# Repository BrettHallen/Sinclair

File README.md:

# Sinclair
Projects for Sinclair computers (ZX80, ZX81, TS1000, TS1500, TS2068, Spectrum and clones such as the Minstrel 2 & 3).

Note!<br>
These projects maybe work-in-progress and thus not completed or fully tested!

## TS1500 Extender
Check out the ZX81 bus extender [here](https://github.com/zxinfo-diy-electronics/zx81-bus-extender) - should do the job!

## [ZX80 Gaming Keyboard](/ZX80_Gaming_Keyboard)
The cursor keys on a ZX80/ZX81 are the 5/6/7/8 numeric keys along the top row.  My simple brain can't readily adapt to this in games like ZX80 KONG or PACMAN so this is just a ZX80/ZX81 compatible keyboard with additional cursor keys.  Designed initially for use with the Minstrel 2 computer (ZX80), but can also be used with the ZX80, Minstrel 3/ZX81 and Minstrel 4th/Jupiter Ace.

### Video
- [Minstrel 2 (Sinclair ZX80 Clone): Part 3 (Gaming Keyboard)](https://youtu.be/veES_CpFuDQ)
- [Gaming Keyboard for ZX80/ZX81/Minstrel/Jupiter Ace: Part 1 (Minstrel 2 Test)](https://youtu.be/O0Em2sR0H4w)

## [ZX80 Pixel Synch](/ZX80_Pixel_Sync)
Small daughterboard to fix the [ZX80's pixel synchronisation](http://blog.tynemouthsoftware.co.uk/2022/09/minstrel-2-pixel-synchronisation-part-1.html) issue on the Minstrel 2 computer v2.8 or earlier.  I have a v2.6 board.  

### Video
[Minstrel 2 (Sinclair ZX80 Clone): Part 2 (Pixel Synch. Issue)](https://youtu.be/O-Urgigq2Vk)

## [ZX81 Centronics](/ZX81_Centronics)
Recreating a DIY centronics interface from German computer magazine c't.<br>

## [ZX81 RAM Upgrade](/ZX81_RAM_Upgrade)
Yes, yes, it's been done many times before.<br>

## [Z88 Serial Port Converter (DE9-to-DB25)](/Z88_Serial_DE9-to-DB25)
I'm finally getting my hands on a Cambridge Computers Z88.  I realised that the [Universal Backpack Drive (UBPD)](https://www.soigeneris.com/universal-backpack-drive) I have for the NEC-PC8201A will also work on the Z88 but requires a converter board.  It's possible to order one from Soigeneris when you order a UBPD and there is an existing design available on [Github](https://github.com/bkw777/Z88_RS232), but I thought I'd also have a crack at it.

### Video
[Cambridge Computer Z88: Part 2 (Backpack Drive - First Attempt)](https://youtu.be/SjToMHrZwcI)

## [Z88 Serial Port Converter (DE9-to-DE9)](/Z88_Serial_DE9_Converter)
Simple board to convert Z88 DE9 serial port to standard DE9 to use with Serial-to-USB converter, for example.

## [Z88 Mechanical Keyboard](/Z88_Mechanical_Keyboard)
The original keyboard on my Z88 seems a bit flaky - let's try designing a nice, modern replacement.

## [VDrive Serial Interface for Z88](/VDriveZ88_Serial_Converter)
Serial interface converter for the Z88 to use a VDrive.

## [ZX26 Computer](/https://github.com/BrettHallen/ZX26_Computer)
My attempt at a ZX81 clone using the vLA81.

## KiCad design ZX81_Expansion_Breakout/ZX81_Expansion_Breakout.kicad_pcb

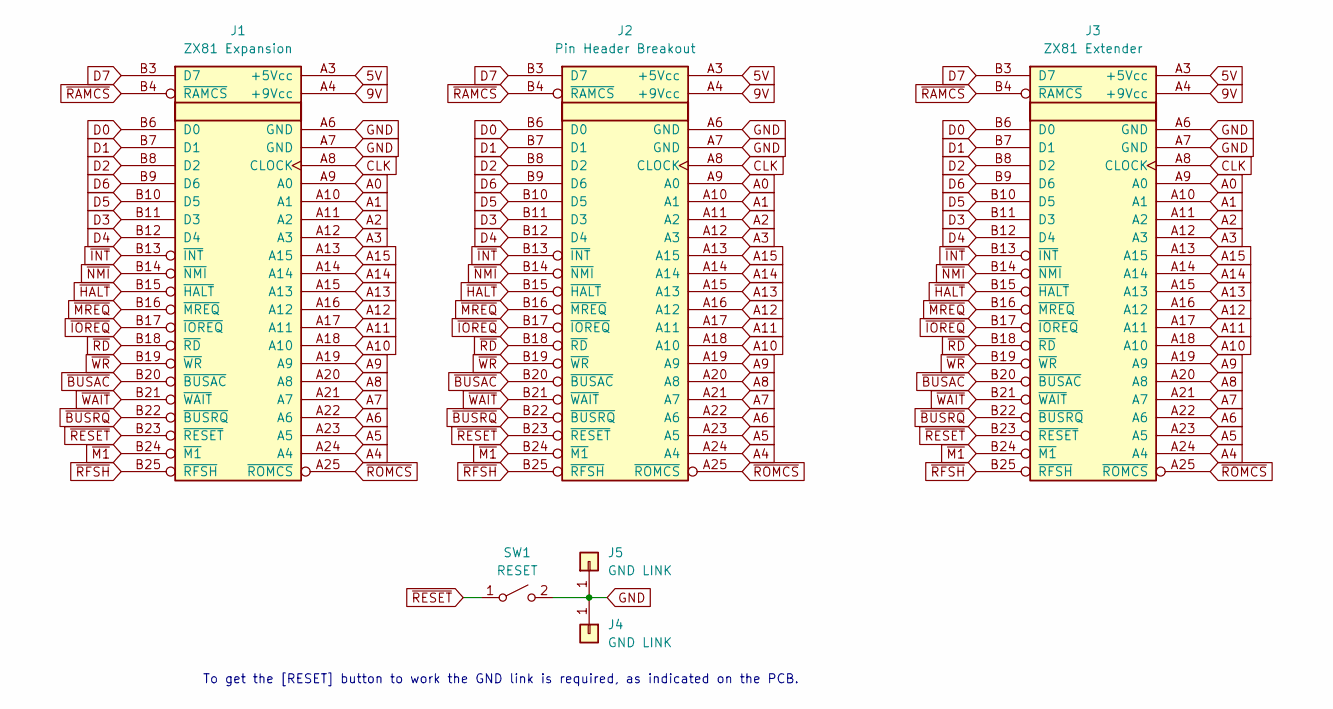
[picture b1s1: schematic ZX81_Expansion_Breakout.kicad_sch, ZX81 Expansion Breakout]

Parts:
J1: ZX81 Expansion; EDGE ZX81 BOTTOM
J2: Pin Header Breakout; PinHeader_2x23_P2.54mm_Vertical
J3: ZX81 Extender; EDGE ZX81 TOP
J4, J5: GND LINK; PinHeader_1x01_P2.54mm_Vertical
SW1: RESET; SW_PUSH_6mm

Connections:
5V: J1.A3 (+5Vcc), J2.A3 (+5Vcc), J3.A3 (+5Vcc)
9V: J1.A4 (+9Vcc), J2.A4 (+9Vcc), J3.A4 (+9Vcc)
A0: J1.A9 (A0), J2.A9 (A0), J3.A9 (A0)
A1: J1.A10 (A1), J2.A10 (A1), J3.A10 (A1)
A2: J1.A11 (A2), J2.A11 (A2), J3.A11 (A2)
A3: J1.A12 (A3), J2.A12 (A3), J3.A12 (A3)
A4: J1.A24 (A4), J2.A24 (A4), J3.A24 (A4)
A5: J1.A23 (A5), J2.A23 (A5), J3.A23 (A5)
A6: J1.A22 (A6), J2.A22 (A6), J3.A22 (A6)
A7: J1.A21 (A7), J2.A21 (A7), J3.A21 (A7)
A8: J1.A20 (A8), J2.A20 (A8), J3.A20 (A8)
A9: J1.A19 (A9), J2.A19 (A9), J3.A19 (A9)
A10: J1.A18 (A10), J2.A18 (A10), J3.A18 (A10)
A11: J1.A17 (A11), J2.A17 (A11), J3.A17 (A11)
A12: J1.A16 (A12), J2.A16 (A12), J3.A16 (A12)
A13: J1.A15 (A13), J2.A15 (A13), J3.A15 (A13)
A14: J1.A14, J2.A14, J3.A14
A15: J1.A13 (A15), J2.A13 (A15), J3.A13 (A15)
CLK: J1.A8 (CLOCK), J2.A8 (CLOCK), J3.A8 (CLOCK)
D0: J1.B6 (D0), J2.B6 (D0), J3.B6 (D0)
D1: J1.B7 (D1), J2.B7 (D1), J3.B7 (D1)
D2: J1.B8 (D2), J2.B8 (D2), J3.B8 (D2)
D3: J1.B11 (D3), J2.B11 (D3), J3.B11 (D3)
D4: J1.B12 (D4), J2.B12 (D4), J3.B12 (D4)
D5: J1.B10 (D5), J2.B10 (D5), J3.B10 (D5)
D6: J1.B9 (D6), J2.B9 (D6), J3.B9 (D6)
D7: J1.B3 (D7), J2.B3 (D7), J3.B3 (D7)
GND: J1.A6 (GND), J1.A7 (GND), J2.A6 (GND), J2.A7 (GND), J3.A6 (GND), J3.A7 (GND), J4.1 (Pin_1_1), J5.1 (Pin_1_1), SW1.2 (B)
~BUSAC: J1.B20 (~BUSAC), J2.B20 (~BUSAC), J3.B20 (~BUSAC)
~BUSRQ: J1.B22 (~BUSRQ), J2.B22 (~BUSRQ), J3.B22 (~BUSRQ)
~HALT: J1.B15 (~HALT), J2.B15 (~HALT), J3.B15 (~HALT)
~INT: J1.B13 (~INT), J2.B13 (~INT), J3.B13 (~INT)
~IOREQ: J1.B17 (~IOREQ), J2.B17 (~IOREQ), J3.B17 (~IOREQ)
~M1: J1.B24 (~M1), J2.B24 (~M1), J3.B24 (~M1)
~MREQ: J1.B16 (~MREQ), J2.B16 (~MREQ), J3.B16 (~MREQ)
~NMI: J1.B14 (~NMI), J2.B14 (~NMI), J3.B14 (~NMI)
~RAMCS: J1.B4 (~RAMCS), J2.B4 (~RAMCS), J3.B4 (~RAMCS)
~RD: J1.B18 (~RD), J2.B18 (~RD), J3.B18 (~RD)
~RESET: J1.B23 (~RESET), J2.B23 (~RESET), J3.B23 (~RESET), SW1.1 (A)
~RFSH: J1.B25 (~RFSH), J2.B25 (~RFSH), J3.B25 (~RFSH)
~ROMCS: J1.A25 (~ROMCS), J2.A25 (~ROMCS), J3.A25 (~ROMCS)
~WAIT: J1.B21 (~WAIT), J2.B21 (~WAIT), J3.B21 (~WAIT)
~WR: J1.B19 (~WR), J2.B19 (~WR), J3.B19 (~WR)

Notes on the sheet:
To get the [RESET] button to work the GND link is required, as indicated on the PCB.

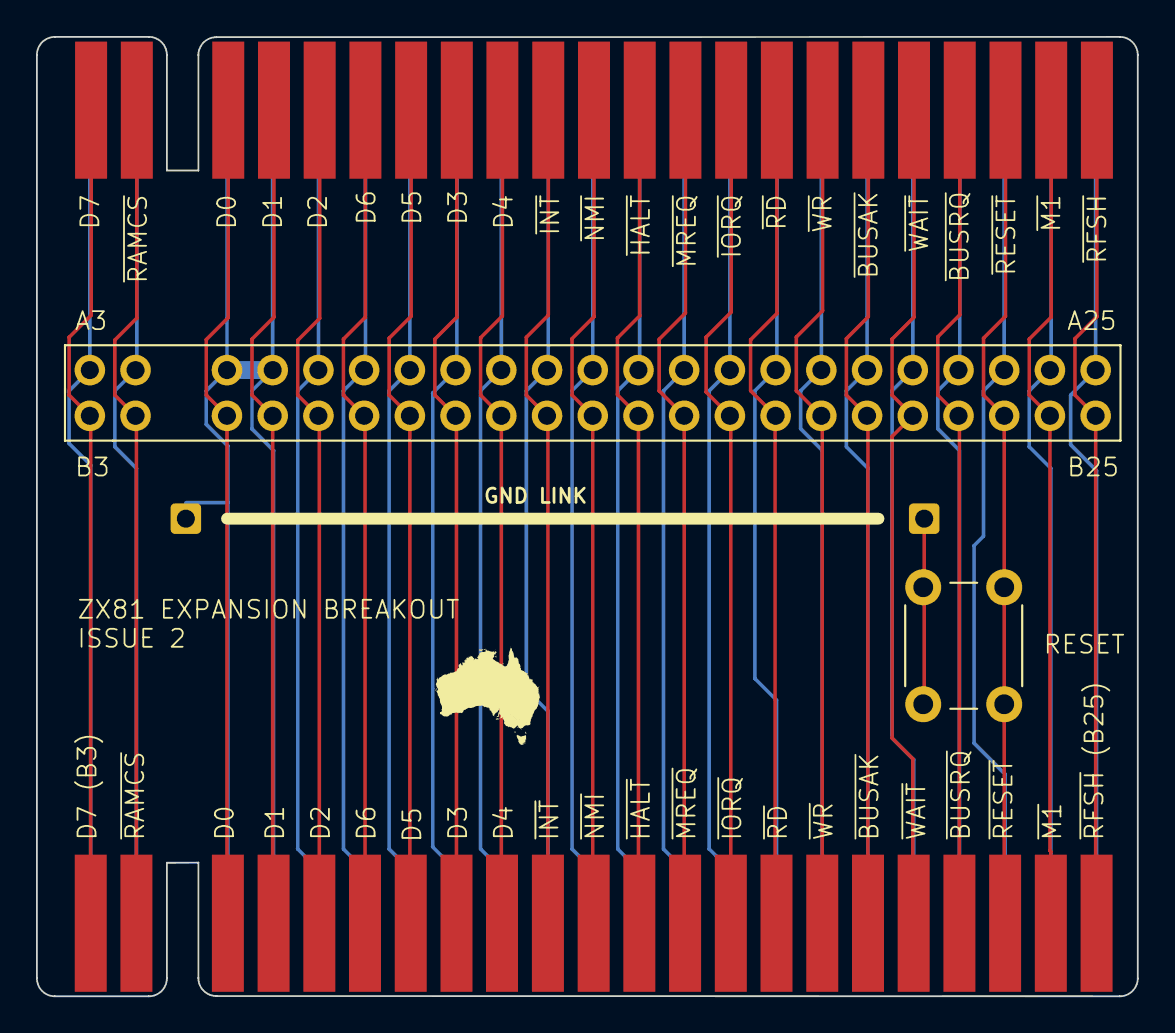
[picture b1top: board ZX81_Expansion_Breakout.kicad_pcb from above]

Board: 2 copper layers, 61.2 x 53.3 mm, 6 parts (0 on the bottom side), 43 nets.

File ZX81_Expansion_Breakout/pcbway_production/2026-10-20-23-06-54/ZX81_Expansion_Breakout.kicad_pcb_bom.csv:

Designator,Quantity,Value,Footprint,Package,MPN,DNP,Mount_Type,Field4,KiLib_Generator,Field5,Description
J1,1,ZX81 Expansion,EDGE ZX81 BOTTOM,,,,tht,SLOT,,,
J2,1,Pin Header Breakout,PinHeader_2x23_P2.54mm_Vertical,,,,tht,,connector/pin_header_socket,,
J3,1,ZX81 Extender,EDGE ZX81 TOP,,,,tht,SLOT,,SLOT,
"J4, J5",2,GND LINK,PinHeader_1x01_P2.54mm_Vertical,,,,tht,,connector/pin_header_socket,,"Generic connector, single row, 01x01, script generated (kicad-library-utils/schlib/autogen/connector/)"
R2,1,LINK,PinHeader_1x02_P2.54mm_Vertical,,,,tht,,connector/pin_header_socket,,Resistor
SW1,1,RESET,SW_PUSH_6mm,,,,tht,,,,Single Pole Single Throw (SPST) switch

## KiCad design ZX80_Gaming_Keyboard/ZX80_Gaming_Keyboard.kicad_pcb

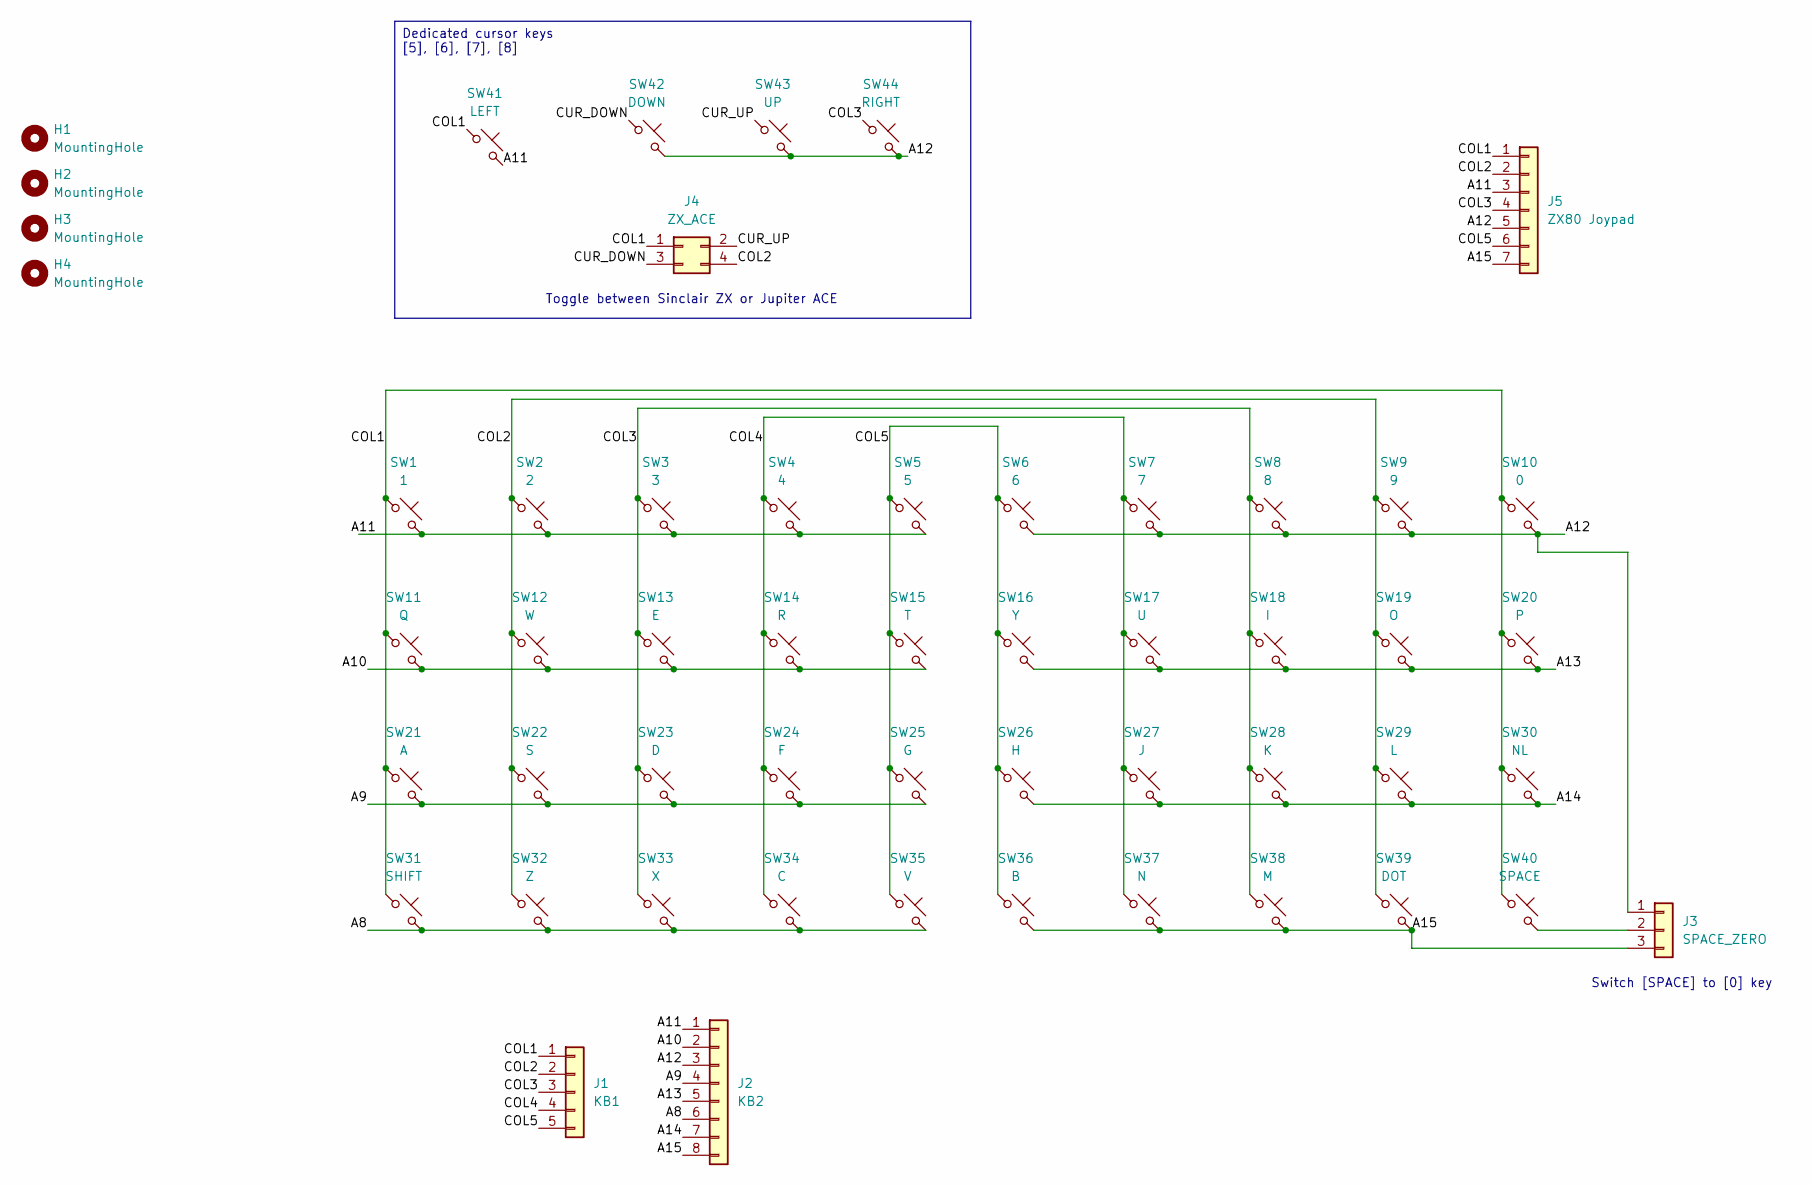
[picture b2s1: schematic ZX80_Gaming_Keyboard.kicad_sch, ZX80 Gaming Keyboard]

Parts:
H1, H2, H3, H4: MountingHole; MountingHole_3.2mm_M3
J1: KB1; PinHeader_1x05_P2.54mm_Vertical
J2: KB2; PinHeader_1x08_P2.54mm_Vertical
J3: SPACE_ZERO; PinHeader_1x03_P2.54mm_Vertical
J4: ZX_ACE; PinHeader_2x02_P2.54mm_Vertical
J5: ZX80 Joypad; PinHeader_1x07_P2.54mm_Vertical
SW1: 1; SW_PUSH-12mm
SW2: 2; SW_PUSH-12mm
SW3: 3; SW_PUSH-12mm
SW4: 4; SW_PUSH-12mm
SW5: 5; SW_PUSH-12mm
SW6: 6; SW_PUSH-12mm
SW7: 7; SW_PUSH-12mm
SW8: 8; SW_PUSH-12mm
SW9: 9; SW_PUSH-12mm
SW10: 0; SW_PUSH-12mm
SW11: Q; SW_PUSH-12mm
SW12: W; SW_PUSH-12mm
SW13: E; SW_PUSH-12mm
SW14: R; SW_PUSH-12mm
SW15: T; SW_PUSH-12mm
SW16: Y; SW_PUSH-12mm
SW17: U; SW_PUSH-12mm
SW18: I; SW_PUSH-12mm
SW19: O; SW_PUSH-12mm
SW20: P; SW_PUSH-12mm
SW21: A; SW_PUSH-12mm
SW22: S; SW_PUSH-12mm
SW23: D; SW_PUSH-12mm
SW24: F; SW_PUSH-12mm
SW25: G; SW_PUSH-12mm
SW26: H; SW_PUSH-12mm
SW27: J; SW_PUSH-12mm
SW28: K; SW_PUSH-12mm
SW29: L; SW_PUSH-12mm
SW30: NL; SW_PUSH-12mm
SW31: SHIFT; SW_PUSH-12mm
SW32: Z; SW_PUSH-12mm
SW33: X; SW_PUSH-12mm
SW34: C; SW_PUSH-12mm
SW35: V; SW_PUSH-12mm
SW36: B; SW_PUSH-12mm
SW37: N; SW_PUSH-12mm
SW38: M; SW_PUSH-12mm
SW39: DOT; SW_PUSH-12mm
SW40: SPACE; SW_PUSH-12mm
SW41: LEFT; SW_PUSH-12mm
SW42: DOWN; SW_PUSH-12mm
SW43: UP; SW_PUSH-12mm
SW44: RIGHT; SW_PUSH-12mm

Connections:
/A8: J2.6, SW31.2, SW32.2, SW33.2, SW34.2, SW35.2
/A9: J2.4, SW21.2, SW22.2, SW23.2, SW24.2, SW25.2
/A10: J2.2, SW11.2, SW12.2, SW13.2, SW14.2, SW15.2
/A11: J2.1, J5.3, SW1.2, SW2.2, SW3.2, SW4.2, SW5.2, SW41.2
/A12: J2.3, J3.1, J5.5, SW6.2, SW7.2, SW8.2, SW9.2, SW10.2, SW42.2, SW43.2, SW44.2
/A13: J2.5, SW16.2, SW17.2, SW18.2, SW19.2, SW20.2
/A14: J2.7, SW26.2, SW27.2, SW28.2, SW29.2, SW30.2
/A15: J2.8, J3.3, J5.7, SW36.2, SW37.2, SW38.2, SW39.2
/COL1: J1.1, J4.1, J5.1, SW1.1, SW10.1, SW11.1, SW20.1, SW21.1, SW30.1, SW31.1, SW40.1, SW41.1
/COL2: J1.2, J4.4, J5.2, SW2.1, SW9.1, SW12.1, SW19.1, SW22.1, SW29.1, SW32.1, SW39.1
/COL3: J1.3, J5.4, SW3.1, SW8.1, SW13.1, SW18.1, SW23.1, SW28.1, SW33.1, SW38.1, SW44.1
/COL4: J1.4, SW4.1, SW7.1, SW14.1, SW17.1, SW24.1, SW27.1, SW34.1, SW37.1
/COL5: J1.5, J5.6, SW5.1, SW6.1, SW15.1, SW16.1, SW25.1, SW26.1, SW35.1, SW36.1
/CUR_DOWN: J4.3, SW42.1
/CUR_UP: J4.2, SW43.1
unnamed: J3.2, SW40.2

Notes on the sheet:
Toggle between Sinclair ZX or Jupiter ACE
Switch [SPACE] to [0] key
Dedicated cursor keys [5], [6], [7], [8]

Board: 2 copper layers, 53 parts (0 on the bottom side), 16 nets, no tracks yet.

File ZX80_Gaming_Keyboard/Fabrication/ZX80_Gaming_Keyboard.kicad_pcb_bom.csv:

Designator,Quantity,Value,Footprint,Package,MPN,DNP,Mount_Type,Description
J1,1,KB1,PinHeader_1x05_P2.54mm_Vertical,,,,tht,"Generic connector, single row, 01x05, script generated (kicad-library-utils/schlib/autogen/connector/)"
J2,1,KB2,PinHeader_1x08_P2.54mm_Vertical,,,,tht,"Generic connector, single row, 01x08, script generated (kicad-library-utils/schlib/autogen/connector/)"
J3,1,SPACE_ZERO,PinHeader_1x03_P2.54mm_Vertical,,,,tht,"Generic connector, single row, 01x03, script generated (kicad-library-utils/schlib/autogen/connector/)"
J4,1,ZX_ACE,PinHeader_2x02_P2.54mm_Vertical,,,,tht,"Generic connector, double row, 02x02, odd/even pin numbering scheme (row 1 odd numbers, row 2 even numbers), script generated (kicad-library-utils/schlib/autogen/connector/)"
SW1,1,1,SW_Cherry_MX_1.00u_PCB,,,,tht,"Push button switch, normally open, two pins, 45° tilted"
SW10,1,0,SW_Cherry_MX_1.00u_PCB,,,,tht,"Push button switch, normally open, two pins, 45° tilted"
SW11,1,Q,SW_Cherry_MX_1.00u_PCB,,,,tht,"Push button switch, normally open, two pins, 45° tilted"
SW12,1,W,SW_Cherry_MX_1.00u_PCB,,,,tht,"Push button switch, normally open, two pins, 45° tilted"
SW13,1,E,SW_Cherry_MX_1.00u_PCB,,,,tht,"Push button switch, normally open, two pins, 45° tilted"
SW14,1,R,SW_Cherry_MX_1.00u_PCB,,,,tht,"Push button switch, normally open, two pins, 45° tilted"
SW15,1,T,SW_Cherry_MX_1.00u_PCB,,,,tht,"Push button switch, normally open, two pins, 45° tilted"
SW16,1,Y,SW_Cherry_MX_1.00u_PCB,,,,tht,"Push button switch, normally open, two pins, 45° tilted"
SW17,1,U,SW_Cherry_MX_1.00u_PCB,,,,tht,"Push button switch, normally open, two pins, 45° tilted"
SW18,1,I,SW_Cherry_MX_1.00u_PCB,,,,tht,"Push button switch, normally open, two pins, 45° tilted"
SW19,1,O,SW_Cherry_MX_1.00u_PCB,,,,tht,"Push button switch, normally open, two pins, 45° tilted"
SW2,1,2,SW_Cherry_MX_1.00u_PCB,,,,tht,"Push button switch, normally open, two pins, 45° tilted"
SW20,1,P,SW_Cherry_MX_1.00u_PCB,,,,tht,"Push button switch, normally open, two pins, 45° tilted"
SW21,1,A,SW_Cherry_MX_1.00u_PCB,,,,tht,"Push button switch, normally open, two pins, 45° tilted"
SW22,1,S,SW_Cherry_MX_1.00u_PCB,,,,tht,"Push button switch, normally open, two pins, 45° tilted"
SW23,1,D,SW_Cherry_MX_1.00u_PCB,,,,tht,"Push button switch, normally open, two pins, 45° tilted"
SW24,1,F,SW_Cherry_MX_1.00u_PCB,,,,tht,"Push button switch, normally open, two pins, 45° tilted"
SW25,1,G,SW_Cherry_MX_1.00u_PCB,,,,tht,"Push button switch, normally open, two pins, 45° tilted"
SW26,1,H,SW_Cherry_MX_1.00u_PCB,,,,tht,"Push button switch, normally open, two pins, 45° tilted"
SW27,1,J,SW_Cherry_MX_1.00u_PCB,,,,tht,"Push button switch, normally open, two pins, 45° tilted"
SW28,1,K,SW_Cherry_MX_1.00u_PCB,,,,tht,"Push button switch, normally open, two pins, 45° tilted"
SW29,1,L,SW_Cherry_MX_1.00u_PCB,,,,tht,"Push button switch, normally open, two pins, 45° tilted"
SW3,1,3,SW_Cherry_MX_1.00u_PCB,,,,tht,"Push button switch, normally open, two pins, 45° tilted"
SW30,1,NL,SW_Cherry_MX_1.00u_PCB,,,,tht,"Push button switch, normally open, two pins, 45° tilted"
SW31,1,SHIFT,SW_Cherry_MX_1.00u_PCB,,,,tht,"Push button switch, normally open, two pins, 45° tilted"
SW32,1,Z,SW_Cherry_MX_1.00u_PCB,,,,tht,"Push button switch, normally open, two pins, 45° tilted"
SW33,1,X,SW_Cherry_MX_1.00u_PCB,,,,tht,"Push button switch, normally open, two pins, 45° tilted"
SW34,1,C,SW_Cherry_MX_1.00u_PCB,,,,tht,"Push button switch, normally open, two pins, 45° tilted"
SW35,1,V,SW_Cherry_MX_1.00u_PCB,,,,tht,"Push button switch, normally open, two pins, 45° tilted"
SW36,1,B,SW_Cherry_MX_1.00u_PCB,,,,tht,"Push button switch, normally open, two pins, 45° tilted"
SW37,1,N,SW_Cherry_MX_1.00u_PCB,,,,tht,"Push button switch, normally open, two pins, 45° tilted"
SW38,1,M,SW_Cherry_MX_1.00u_PCB,,,,tht,"Push button switch, normally open, two pins, 45° tilted"
SW39,1,DOT,SW_Cherry_MX_1.00u_PCB,,,,tht,"Push button switch, normally open, two pins, 45° tilted"
SW4,1,4,SW_Cherry_MX_1.00u_PCB,,,,tht,"Push button switch, normally open, two pins, 45° tilted"
SW40,1,SPACE,SW_Cherry_MX_1.00u_PCB,,,,tht,"Push button switch, normally open, two pins, 45° tilted"
SW41,1,LEFT,SW_Cherry_MX_1.00u_PCB,,,,tht,"Push button switch, normally open, two pins, 45° tilted"
SW42,1,DOWN,SW_Cherry_MX_1.00u_PCB,,,,tht,"Push button switch, normally open, two pins, 45° tilted"
SW43,1,UP,SW_Cherry_MX_1.00u_PCB,,,,tht,"Push button switch, normally open, two pins, 45° tilted"
SW44,1,RIGHT,SW_Cherry_MX_1.00u_PCB,,,,tht,"Push button switch, normally open, two pins, 45° tilted"
SW5,1,5,SW_Cherry_MX_1.00u_PCB,,,,tht,"Push button switch, normally open, two pins, 45° tilted"
SW6,1,6,SW_Cherry_MX_1.00u_PCB,,,,tht,"Push button switch, normally open, two pins, 45° tilted"
SW7,1,7,SW_Cherry_MX_1.00u_PCB,,,,tht,"Push button switch, normally open, two pins, 45° tilted"
SW8,1,8,SW_Cherry_MX_1.00u_PCB,,,,tht,"Push button switch, normally open, two pins, 45° tilted"
SW9,1,9,SW_Cherry_MX_1.00u_PCB,,,,tht,"Push button switch, normally open, two pins, 45° tilted"

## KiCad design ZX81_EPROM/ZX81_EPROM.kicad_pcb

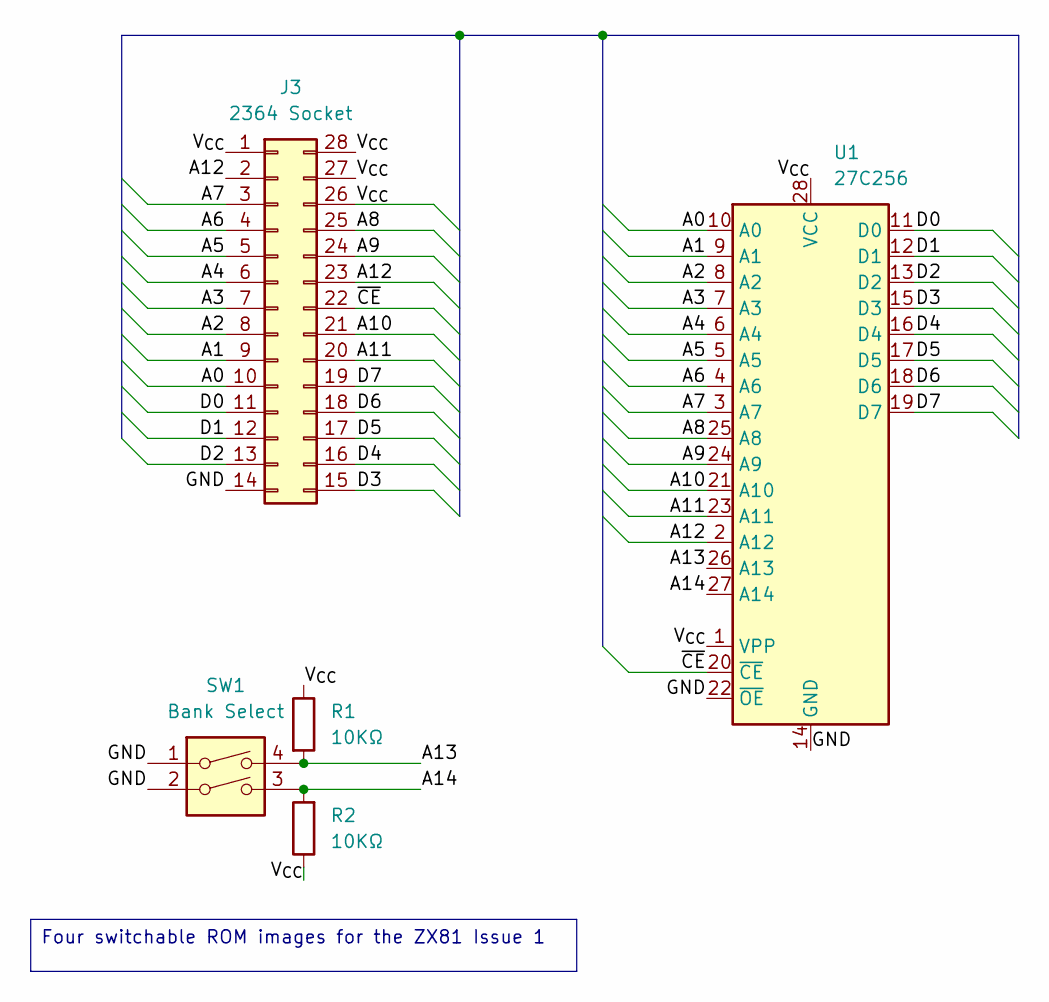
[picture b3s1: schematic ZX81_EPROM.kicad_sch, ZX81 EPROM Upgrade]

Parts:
J3: 2364 Socket; DIP-28_W15.24mm_Socket
R1, R2: 10KΩ; R_0805_2012Metric_Pad1.20x1.40mm_HandSolder
SW1: Bank Select; SW_DIP_SPSTx02_Slide_9.78x7.26mm_W7.62mm_P2.54mm
U1: 27C256; DIP-28_W15.24mm

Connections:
/A0: J3.10, U1.10 (A0)
/A1: J3.9, U1.9 (A1)
/A2: J3.8, U1.8 (A2)
/A3: J3.7, U1.7 (A3)
/A4: J3.6, U1.6 (A4)
/A5: J3.5, U1.5 (A5)
/A6: J3.4, U1.4 (A6)
/A7: J3.3, U1.3 (A7)
/A8: J3.25, U1.25 (A8)
/A9: J3.24, U1.24 (A9)
/A10: J3.21, U1.21 (A10)
/A11: J3.20, U1.23 (A11)
/A12: J3.2, J3.23, U1.2 (A12)
/A13: R1.2, SW1.4, U1.26 (A13)
/A14: R2.2, SW1.3, U1.27 (A14)
/D0: J3.11, U1.11 (D0)
/D1: J3.12, U1.12 (D1)
/D2: J3.13, U1.13 (D2)
/D3: J3.15, U1.15 (D3)
/D4: J3.16, U1.16 (D4)
/D5: J3.17, U1.17 (D5)
/D6: J3.18, U1.18 (D6)
/D7: J3.19, U1.19 (D7)
/GND: J3.14, SW1.1, SW1.2, U1.14 (GND), U1.22 (~OE)
/V_{CC}: J3.1, J3.26, J3.27, J3.28, R1.1, R2.1, U1.1 (VPP), U1.28 (VCC)
/~CE: J3.22, U1.20 (~CE)

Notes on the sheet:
Four switchable ROM images for the ZX81 Issue 1

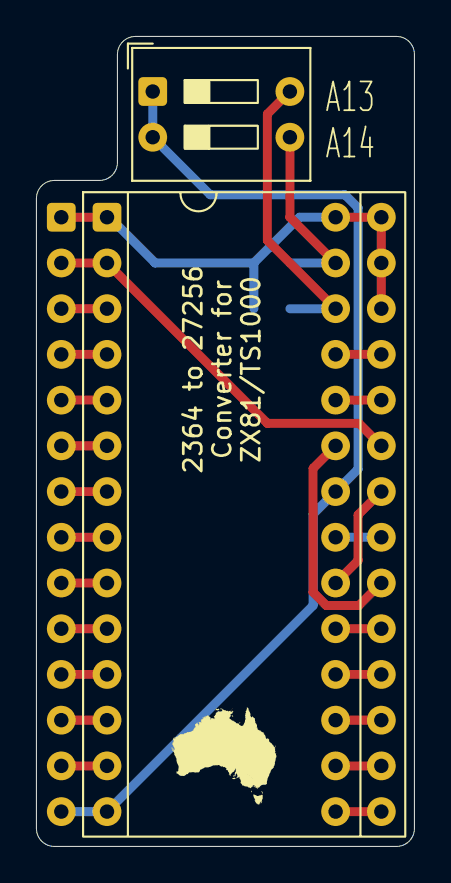
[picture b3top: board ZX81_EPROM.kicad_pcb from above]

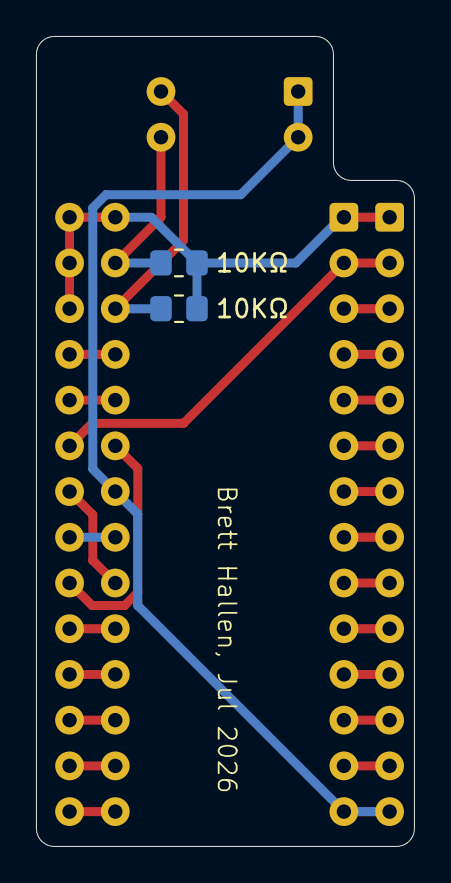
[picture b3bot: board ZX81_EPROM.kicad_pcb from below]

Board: 2 copper layers, 21.0 x 45.0 mm, 5 parts (2 on the bottom side), 26 nets.

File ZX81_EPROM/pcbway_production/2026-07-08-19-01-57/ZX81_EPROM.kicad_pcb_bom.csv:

Designator,Quantity,Value,Footprint,Package,MPN,DNP,Mount_Type,Description,KiLib_Generator
J3,1,2364 Socket,DIP-28_W15.24mm_Socket,,,,tht,"Generic connector, double row, 02x14, counter clockwise pin numbering scheme (similar to DIP package numbering), script generated (kicad-library-utils/schlib/autogen/connector/)",package/DIP/legacy
"R1, R2",2,10KΩ,R_0805_2012Metric_Pad1.20x1.40mm_HandSolder,,,,smt,Resistor,SMD_2terminal_chip_molded
SW1,1,Bank Select,SW_DIP_SPSTx02_Slide_9.78x7.26mm_W7.62mm_P2.54mm,,,,tht,"2x DIP Switch, Single Pole Single Throw (SPST) switch, small symbol",button_switch/DIP
U1,1,27C256,DIP-28_W15.24mm,,,,tht,OTP EPROM 256 KiBit,package/DIP/legacy

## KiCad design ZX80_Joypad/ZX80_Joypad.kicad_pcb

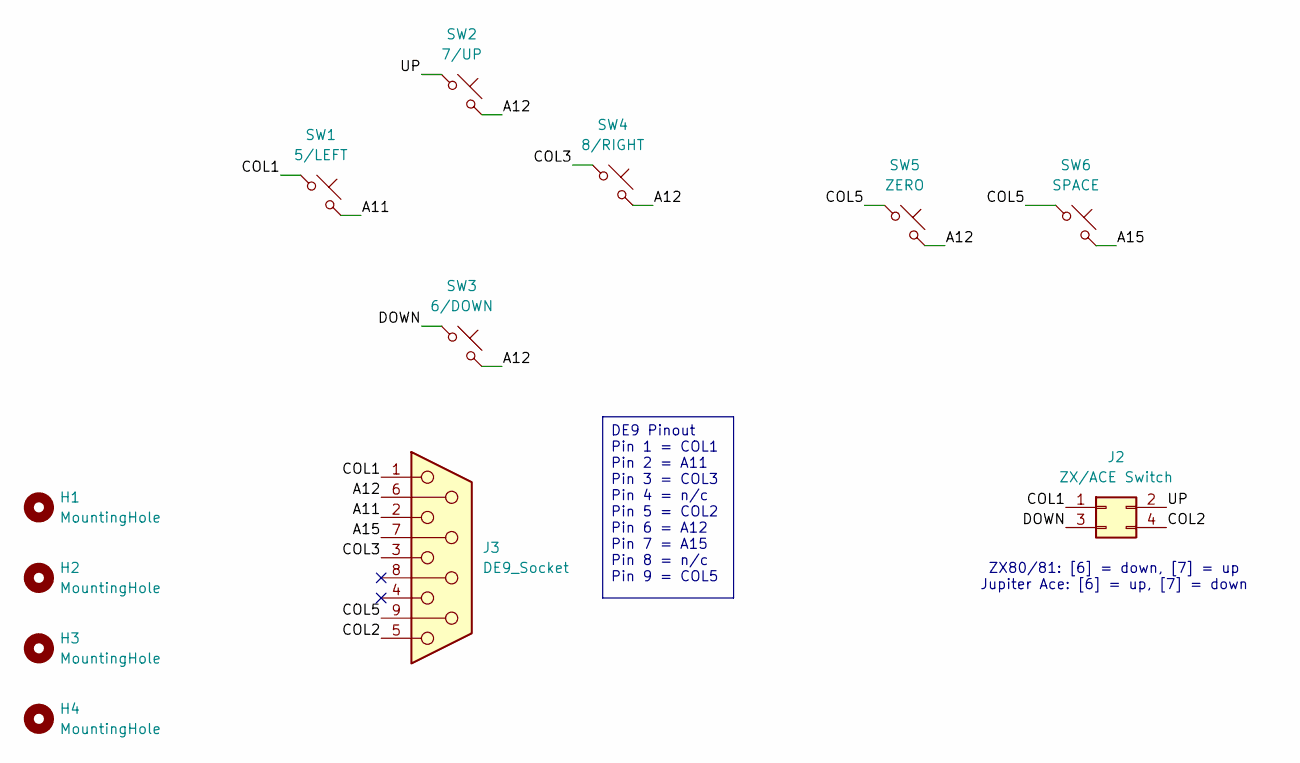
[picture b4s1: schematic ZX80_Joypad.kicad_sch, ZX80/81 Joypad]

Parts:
H1, H2, H3, H4: MountingHole; MountingHole_3.2mm_M3_DIN965
J2: ZX/ACE Switch; PinHeader_2x02_P2.54mm_Vertical
J3: DE9_Socket; DSUB-9_Socket_EdgeMount_P2.77mm
SW1: 5/LEFT; SW_PUSH-12mm
SW2: 7/UP; SW_PUSH-12mm
SW3: 6/DOWN; SW_PUSH-12mm
SW4: 8/RIGHT; SW_PUSH-12mm
SW5: ZERO; SW_PUSH-12mm
SW6: SPACE; SW_PUSH-12mm

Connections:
/A11: J3.2, SW1.2
/A12: J3.6, SW2.2, SW3.2, SW4.2, SW5.2
/A15: J3.7, SW6.2
/COL1: J2.1, J3.1, SW1.1
/COL2: J2.4, J3.5
/COL3: J3.3, SW4.1
/COL5: J3.9, SW5.1, SW6.1
/DOWN: J2.3, SW3.1
/UP: J2.2, SW2.1

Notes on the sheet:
ZX80/81: [6] = down, [7] = up Jupiter Ace: [6] = up, [7] = down
DE9 Pinout Pin 1 = COL1 Pin 2 = A11 Pin 3 = COL3 Pin 4 = n/c Pin 5 = COL2 Pin 6 = A12 Pin 7 = A15 Pin 8 = n/c Pin 9 = COL5

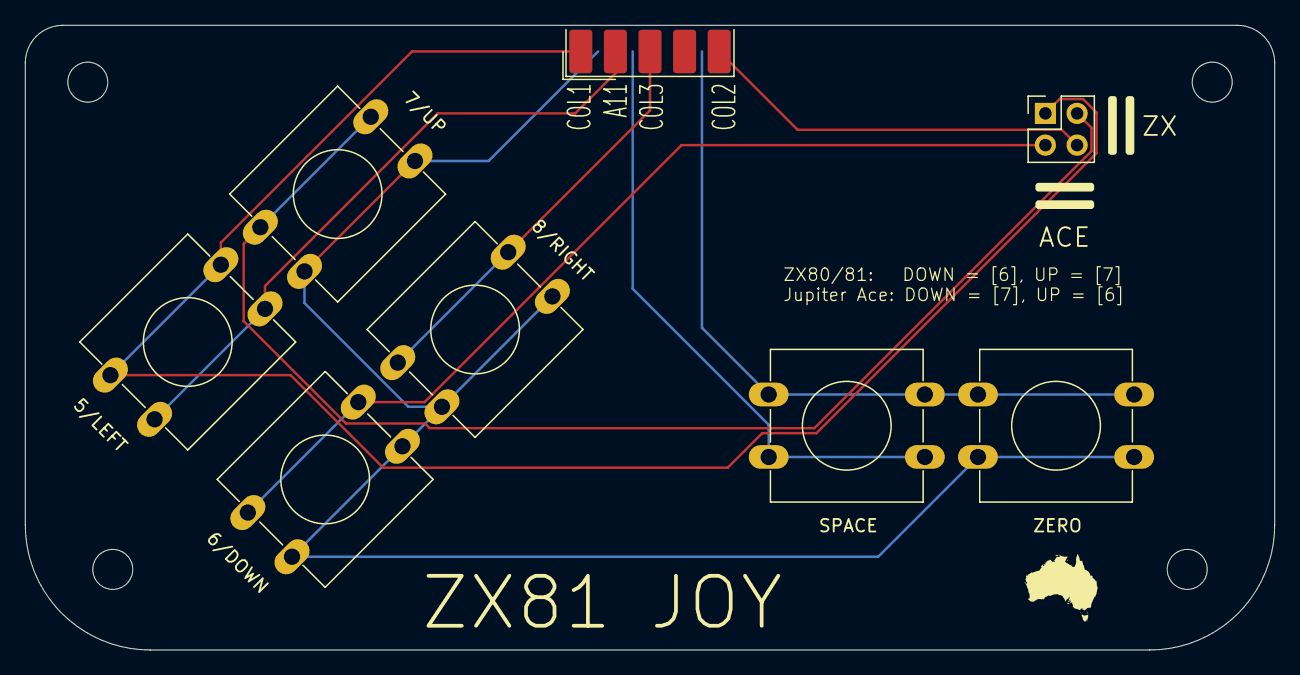
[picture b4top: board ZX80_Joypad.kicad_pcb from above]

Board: 2 copper layers, 100.0 x 50.0 mm, 12 parts (0 on the bottom side), 9 nets.

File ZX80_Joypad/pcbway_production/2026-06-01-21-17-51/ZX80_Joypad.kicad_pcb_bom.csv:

Designator,Quantity,Value,Footprint,Package,MPN,DNP,Mount_Type,Description
J1,1,Conn_02x04_Odd_Even,PinHeader_2x04_P2.54mm_Vertical,,,,tht,"Generic connector, double row, 02x04, odd/even pin numbering scheme (row 1 odd numbers, row 2 even numbers), script generated (kicad-library-utils/schlib/autogen/connector/)"
J2,1,ZX/ACE Switch,PinHeader_2x02_P2.54mm_Vertical,,,,tht,"Generic connector, double row, 02x02, odd/even pin numbering scheme (row 1 odd numbers, row 2 even numbers), script generated (kicad-library-utils/schlib/autogen/connector/)"
SW1,1,5/LEFT,SW_PUSH-12mm,,,,tht,"Push button switch, normally open, two pins, 45° tilted"
SW2,1,7/UP,SW_PUSH-12mm,,,,tht,"Push button switch, normally open, two pins, 45° tilted"
SW3,1,6/DOWN,SW_PUSH-12mm,,,,tht,"Push button switch, normally open, two pins, 45° tilted"
SW4,1,8/RIGHT,SW_PUSH-12mm,,,,tht,"Push button switch, normally open, two pins, 45° tilted"
SW5,1,ZERO,SW_PUSH-12mm,,,,tht,"Push button switch, normally open, two pins, 45° tilted"
SW6,1,SPACE,SW_PUSH-12mm,,,,tht,"Push button switch, normally open, two pins, 45° tilted"

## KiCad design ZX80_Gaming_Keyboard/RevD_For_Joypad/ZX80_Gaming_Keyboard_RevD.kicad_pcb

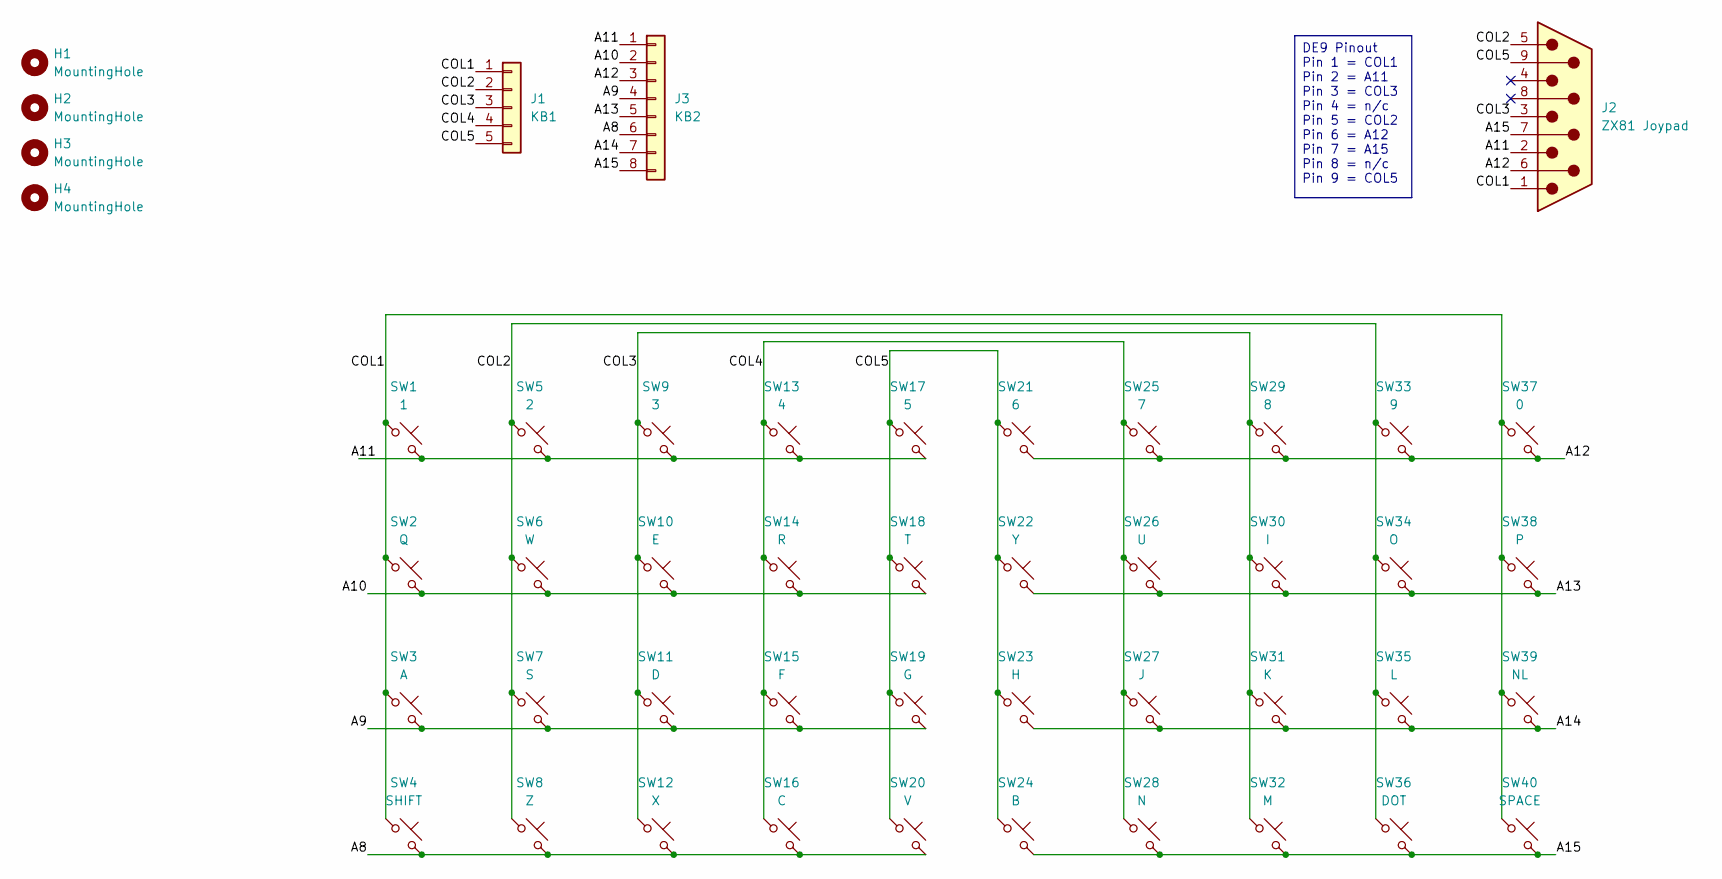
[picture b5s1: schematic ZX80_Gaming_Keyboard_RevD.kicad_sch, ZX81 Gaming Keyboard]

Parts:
H1, H2, H3, H4: MountingHole; MountingHole_3.2mm_M3
J1: KB1; PinHeader_1x05_P2.54mm_Vertical
J2: ZX81 Joypad; DSUB-9_Pins_EdgeMount_P2.77mm
J3: KB2; PinHeader_1x08_P2.54mm_Vertical
SW1: 1; SW_Gateron_LowProfile_THT
SW2: Q; SW_Gateron_LowProfile_THT
SW3: A; SW_Gateron_LowProfile_THT
SW4: SHIFT; SW_Gateron_LowProfile_THT
SW5: 2; SW_Gateron_LowProfile_THT
SW6: W; SW_Gateron_LowProfile_THT
SW7: S; SW_Gateron_LowProfile_THT
SW8: Z; SW_Gateron_LowProfile_THT
SW9: 3; SW_Gateron_LowProfile_THT
SW10: E; SW_Gateron_LowProfile_THT
SW11: D; SW_Gateron_LowProfile_THT
SW12: X; SW_Gateron_LowProfile_THT
SW13: 4; SW_Gateron_LowProfile_THT
SW14: R; SW_Gateron_LowProfile_THT
SW15: F; SW_Gateron_LowProfile_THT
SW16: C; SW_Gateron_LowProfile_THT
SW17: 5; SW_Gateron_LowProfile_THT
SW18: T; SW_Gateron_LowProfile_THT
SW19: G; SW_Gateron_LowProfile_THT
SW20: V; SW_Gateron_LowProfile_THT
SW21: 6; SW_Gateron_LowProfile_THT
SW22: Y; SW_Gateron_LowProfile_THT
SW23: H; SW_Gateron_LowProfile_THT
SW24: B; SW_Gateron_LowProfile_THT
SW25: 7; SW_Gateron_LowProfile_THT
SW26: U; SW_Gateron_LowProfile_THT
SW27: J; SW_Gateron_LowProfile_THT
SW28: N; SW_Gateron_LowProfile_THT
SW29: 8; SW_Gateron_LowProfile_THT
SW30: I; SW_Gateron_LowProfile_THT
SW31: K; SW_Gateron_LowProfile_THT
SW32: M; SW_Gateron_LowProfile_THT
SW33: 9; SW_Gateron_LowProfile_THT
SW34: O; SW_Gateron_LowProfile_THT
SW35: L; SW_Gateron_LowProfile_THT
SW36: DOT; SW_Gateron_LowProfile_THT
SW37: 0; SW_Gateron_LowProfile_THT
SW38: P; SW_Gateron_LowProfile_THT
SW39: NL; SW_Gateron_LowProfile_THT
SW40: SPACE; SW_Gateron_LowProfile_THT

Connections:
/A8: J3.6, SW4.2, SW8.2, SW12.2, SW16.2, SW20.2
/A9: J3.4, SW3.2, SW7.2, SW11.2, SW15.2, SW19.2
/A10: J3.2, SW2.2, SW6.2, SW10.2, SW14.2, SW18.2
/A11: J2.2, J3.1, SW1.2, SW5.2, SW9.2, SW13.2, SW17.2
/A12: J2.6, J3.3, SW21.2, SW25.2, SW29.2, SW33.2, SW37.2
/A13: J3.5, SW22.2, SW26.2, SW30.2, SW34.2, SW38.2
/A14: J3.7, SW23.2, SW27.2, SW31.2, SW35.2, SW39.2
/A15: J2.7, J3.8, SW24.2, SW28.2, SW32.2, SW36.2, SW40.2
/COL1: J1.1, J2.1, SW1.1, SW2.1, SW3.1, SW4.1, SW37.1, SW38.1, SW39.1, SW40.1
/COL2: J1.2, J2.5, SW5.1, SW6.1, SW7.1, SW8.1, SW33.1, SW34.1, SW35.1, SW36.1
/COL3: J1.3, J2.3, SW9.1, SW10.1, SW11.1, SW12.1, SW29.1, SW30.1, SW31.1, SW32.1
/COL4: J1.4, SW13.1, SW14.1, SW15.1, SW16.1, SW25.1, SW26.1, SW27.1, SW28.1
/COL5: J1.5, J2.9, SW17.1, SW18.1, SW19.1, SW20.1, SW21.1, SW22.1, SW23.1, SW24.1

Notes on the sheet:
DE9 Pinout Pin 1 = COL1 Pin 2 = A11 Pin 3 = COL3 Pin 4 = n/c Pin 5 = COL2 Pin 6 = A12 Pin 7 = A15 Pin 8 = n/c Pin 9 = COL5
